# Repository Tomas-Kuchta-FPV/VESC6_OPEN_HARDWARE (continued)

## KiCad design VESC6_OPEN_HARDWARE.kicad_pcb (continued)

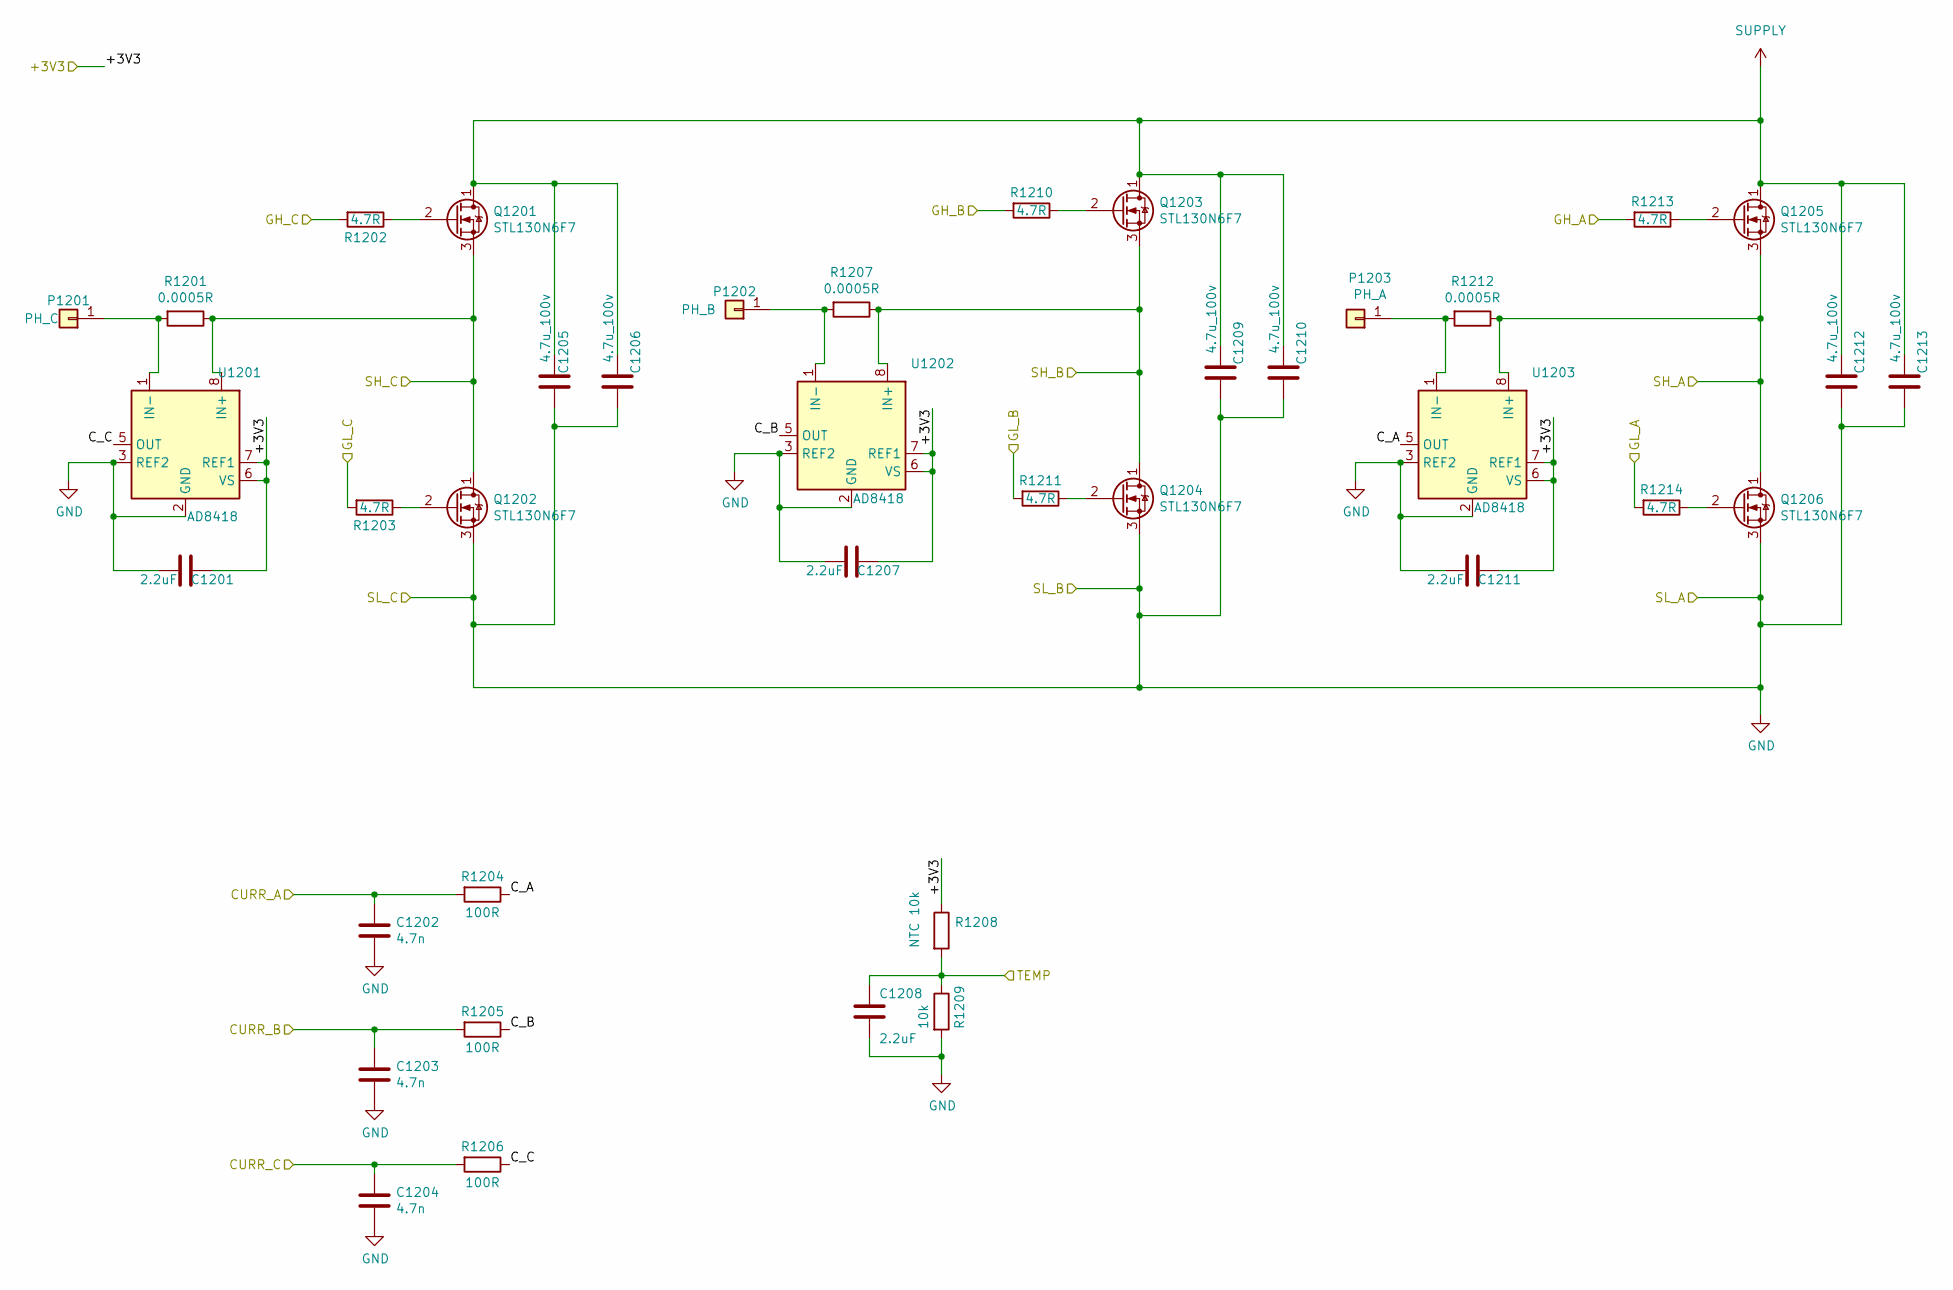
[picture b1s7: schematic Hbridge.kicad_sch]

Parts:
C1201, C1207, C1208, C1211: 2.2uF; C_0603_1608Metric; LCSC C23630
C1202, C1203, C1204: 4.7n; C_0603_1608Metric; LCSC C53987
C1205, C1206, C1209, C1210, C1212, C1213: 4.7u_100v; C_1210_3225Metric; LCSC C385987
P1201: PH_C; Pin_D1.3mm_L11.0mm_LooseFit; LCSC C7200700
P1202: PH_B; Pin_D1.3mm_L11.0mm_LooseFit; LCSC C7200700
P1203: PH_A; Pin_D1.3mm_L11.0mm_LooseFit; LCSC C7200700
Q1201, Q1202, Q1203, Q1204, Q1205, Q1206: STL130N6F7; NVMFS5C612NL; LCSC C501008
R1201, R1207, R1212: 0.0005R; 2512_SHUNT; LCSC C469426
R1202, R1203, R1210, R1211, R1213, R1214: 4.7R; R_0603_1608Metric; LCSC C23164
R1204, R1205, R1206: 100R; R_0603_1608Metric; LCSC C22775
R1208: NTC 10k; R_0603_1608Metric; LCSC C76589
R1209: 10k; R_0603_1608Metric; LCSC C25804
U1201, U1202, U1203: AD8418; SOIC-8_3.9x4.9mm_P1.27mm; LCSC C495342

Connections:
+3V3a: C1201.1, C1207.1, C1211.1, R1208.1, U1201.6 (VS), U1201.7 (REF1), U1202.6 (VS), U1202.7 (REF1), U1203.6 (VS), U1203.7 (REF1); also elsewhere on the board
/CHa/DRV8301/GH_A: R1213.2; also elsewhere on the board
/CHa/DRV8301/GH_B: R1210.2; also elsewhere on the board
/CHa/DRV8301/GH_C: R1202.2; also elsewhere on the board
/CHa/DRV8301/GL_A: R1214.2; also elsewhere on the board
/CHa/DRV8301/GL_B: R1211.2; also elsewhere on the board
/CHa/DRV8301/GL_C: R1203.2; also elsewhere on the board
/CHa/DRV8301/SH_A: Q1205.3 (S), Q1206.1 (D), R1212.1, U1203.8 (IN+); also elsewhere on the board
/CHa/DRV8301/SH_B: Q1203.3 (S), Q1204.1 (D), R1207.1, U1202.8 (IN+); also elsewhere on the board
/CHa/DRV8301/SH_C: Q1201.3 (S), Q1202.1 (D), R1201.1, U1201.8 (IN+); also elsewhere on the board
/CHa/Hbridge/CURR_A: C1202.1, R1204.2; also elsewhere on the board
/CHa/Hbridge/CURR_B: C1203.1, R1205.2; also elsewhere on the board
/CHa/Hbridge/CURR_C: C1204.1, R1206.2; also elsewhere on the board
/CHa/Hbridge/C_A: R1204.1, U1203.5 (OUT)
/CHa/Hbridge/C_B: R1205.1, U1202.5 (OUT)
/CHa/Hbridge/C_C: R1206.1, U1201.5 (OUT)
/CHa/Hbridge/TEMP: C1208.1, R1208.2, R1209.1; also elsewhere on the board
GND: C1201.2, C1202.2, C1203.2, C1204.2, C1205.2, C1206.2, C1207.2, C1208.2, C1209.2, C1210.2, C1211.2, C1212.2, C1213.2, Q1202.3 (S), Q1204.3 (S), Q1206.3 (S), R1209.2, U1201.2 (GND), U1201.3 (REF2), U1202.2 (GND), U1202.3 (REF2), U1203.2 (GND), U1203.3 (REF2); also elsewhere on the board
unnamed: P1201.1 (Pin_1_1), R1201.2, U1201.1 (IN-)
unnamed: P1202.1 (Pin_1_1), R1207.2, U1202.1 (IN-)
unnamed: P1203.1 (Pin_1_1), R1212.2, U1203.1 (IN-)
unnamed: Q1201.2 (G), R1202.1
unnamed: Q1202.2 (G), R1203.1
unnamed: Q1203.2 (G), R1210.1
unnamed: Q1204.2 (G), R1211.1
unnamed: Q1205.2 (G), R1213.1
unnamed: Q1206.2 (G), R1214.1
SUPPLY: C1205.1, C1206.1, C1209.1, C1210.1, C1212.1, C1213.1, Q1201.1 (D), Q1203.1 (D), Q1205.1 (D); also elsewhere on the board

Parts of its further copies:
C2201, C2207, C2208, C2211: 2.2uF; C_0603_1608Metric; LCSC C23630
C2202, C2203, C2204: 4.7n; C_0603_1608Metric; LCSC C53987
C2205, C2206, C2209, C2210, C2212, C2213: 4.7u_100v; C_1210_3225Metric; LCSC C385987
P2201: PH_C; Pin_D1.3mm_L11.0mm_LooseFit; LCSC C7200700
P2202: PH_B; Pin_D1.3mm_L11.0mm_LooseFit; LCSC C7200700
P2203: PH_A; Pin_D1.3mm_L11.0mm_LooseFit; LCSC C7200700
Q2201, Q2202, Q2203, Q2204, Q2205, Q2206: STL130N6F7; NVMFS5C612NL; LCSC C501008
R2201, R2207, R2212: 0.0005R; 2512_SHUNT; LCSC C469426
R2202, R2203, R2210, R2211, R2213, R2214: 4.7R; R_0603_1608Metric; LCSC C23164
R2204, R2205, R2206: 100R; R_0603_1608Metric; LCSC C22775
R2208: NTC 10k; R_0603_1608Metric; LCSC C76589
R2209: 10k; R_0603_1608Metric; LCSC C25804
U2201, U2202, U2203: AD8418; SOIC-8_3.9x4.9mm_P1.27mm; LCSC C495342

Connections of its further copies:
+3V3b: C2201.1, C2207.1, C2211.1, R2208.1, U2201.6 (VS), U2201.7 (REF1), U2202.6 (VS), U2202.7 (REF1), U2203.6 (VS), U2203.7 (REF1); also elsewhere on the board
/CHb/DRV8301/GH_A: R2213.2; also elsewhere on the board
/CHb/DRV8301/GH_B: R2210.2; also elsewhere on the board
/CHb/DRV8301/GH_C: R2202.2; also elsewhere on the board
/CHb/DRV8301/GL_A: R2214.2; also elsewhere on the board
/CHb/DRV8301/GL_B: R2211.2; also elsewhere on the board
/CHb/DRV8301/GL_C: R2203.2; also elsewhere on the board
/CHb/DRV8301/SH_A: Q2205.3 (S), Q2206.1 (D), R2212.1, U2203.8 (IN+); also elsewhere on the board
/CHb/DRV8301/SH_B: Q2203.3 (S), Q2204.1 (D), R2207.1, U2202.8 (IN+); also elsewhere on the board
/CHb/DRV8301/SH_C: Q2201.3 (S), Q2202.1 (D), R2201.1, U2201.8 (IN+); also elsewhere on the board
/CHb/Hbridge/CURR_A: C2202.1, R2204.2; also elsewhere on the board
/CHb/Hbridge/CURR_B: C2203.1, R2205.2; also elsewhere on the board
/CHb/Hbridge/CURR_C: C2204.1, R2206.2; also elsewhere on the board
/CHb/Hbridge/C_A: R2204.1, U2203.5 (OUT)
/CHb/Hbridge/C_B: R2205.1, U2202.5 (OUT)
/CHb/Hbridge/C_C: R2206.1, U2201.5 (OUT)
/CHb/Hbridge/TEMP: C2208.1, R2208.2, R2209.1; also elsewhere on the board
GND: C2201.2, C2202.2, C2203.2, C2204.2, C2205.2, C2206.2, C2207.2, C2208.2, C2209.2, C2210.2, C2211.2, C2212.2, C2213.2, Q2202.3 (S), Q2204.3 (S), Q2206.3 (S), R2209.2, U2201.2 (GND), U2201.3 (REF2), U2202.2 (GND), U2202.3 (REF2), U2203.2 (GND), U2203.3 (REF2); also elsewhere on the board
unnamed: P2201.1 (Pin_1_1), R2201.2, U2201.1 (IN-)
unnamed: P2202.1 (Pin_1_1), R2207.2, U2202.1 (IN-)
unnamed: P2203.1 (Pin_1_1), R2212.2, U2203.1 (IN-)
unnamed: Q2201.2 (G), R2202.1
unnamed: Q2202.2 (G), R2203.1
unnamed: Q2203.2 (G), R2210.1
unnamed: Q2204.2 (G), R2211.1
unnamed: Q2205.2 (G), R2213.1
unnamed: Q2206.2 (G), R2214.1
SUPPLY: C2205.1, C2206.1, C2209.1, C2210.1, C2212.1, C2213.1, Q2201.1 (D), Q2203.1 (D), Q2205.1 (D); also elsewhere on the board

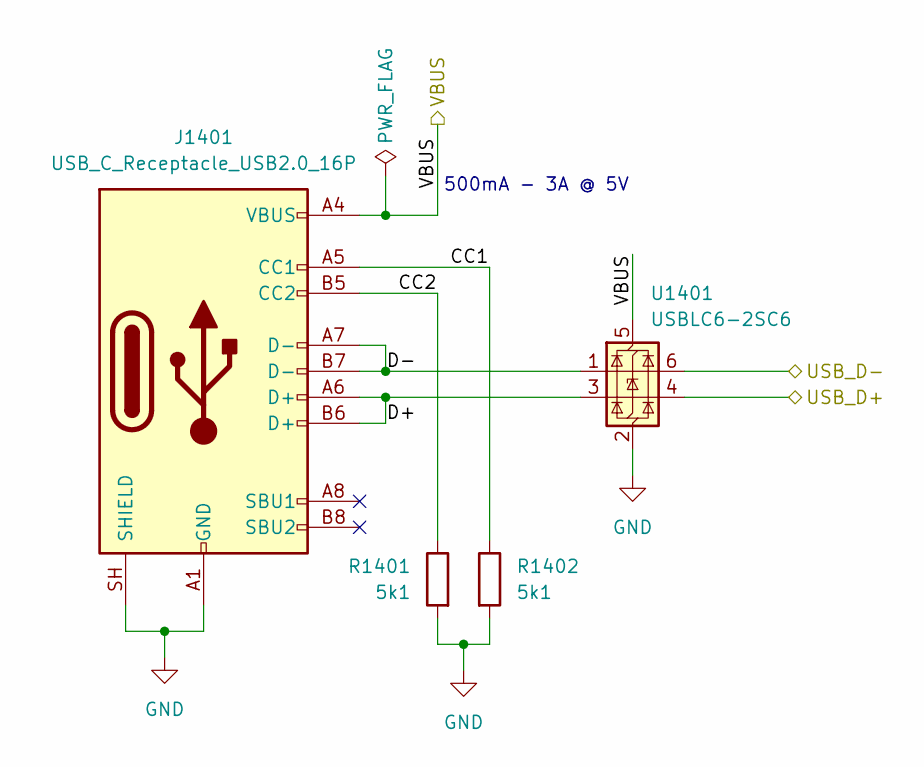
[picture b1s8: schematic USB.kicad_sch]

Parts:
J1401: USB_C_Receptacle_USB2.0_16P; USB_C_Receptacle_HRO_TYPE-C-31-M-12; LCSC part no. C165948
R1401, R1402: 5k1; R_0805_2012Metric_Pad1.20x1.40mm_HandSolder; LCSC part no. C84375
U1401: USBLC6-2SC6; SOT-23-6; LCSC part no. C2827654

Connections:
/CHa/USB/CC1: J1401.A5 (CC1), R1402.1
/CHa/USB/CC2: J1401.B5 (CC2), R1401.1
/CHa/USB/D+: J1401.A6 (D+), J1401.B6 (D+), U1401.3 (I/O2)
/CHa/USB/D-: J1401.A7 (D-), J1401.B7 (D-), U1401.1 (I/O1)
/CHa/USB/USB_D+: U1401.4 (I/O2); also elsewhere on the board
/CHa/USB/USB_D-: U1401.6 (I/O1); also elsewhere on the board
/CHa/USB/VBUS: J1401.A4 (VBUS), J1401.A9 (VBUS), J1401.B4 (VBUS), J1401.B9 (VBUS), U1401.5 (VBUS); also elsewhere on the board
GND: J1401.A1 (GND), J1401.A12 (GND), J1401.B1 (GND), J1401.B12 (GND), J1401.SH (SHIELD), R1401.2, R1402.2, U1401.2 (GND); also elsewhere on the board

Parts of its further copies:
J2401: USB_C_Receptacle_USB2.0_16P; USB_C_Receptacle_HRO_TYPE-C-31-M-12; LCSC part no. C165948
R2401, R2402: 5k1; R_0805_2012Metric_Pad1.20x1.40mm_HandSolder; LCSC part no. C84375
U2401: USBLC6-2SC6; SOT-23-6; LCSC part no. C2827654

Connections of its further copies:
/CHb/USB/CC1: J2401.A5 (CC1), R2402.1
/CHb/USB/CC2: J2401.B5 (CC2), R2401.1
/CHb/USB/D+: J2401.A6 (D+), J2401.B6 (D+), U2401.3 (I/O2)
/CHb/USB/D-: J2401.A7 (D-), J2401.B7 (D-), U2401.1 (I/O1)
/CHb/USB/USB_D+: U2401.4 (I/O2); also elsewhere on the board
/CHb/USB/USB_D-: U2401.6 (I/O1); also elsewhere on the board
/CHb/USB/VBUS: J2401.A4 (VBUS), J2401.A9 (VBUS), J2401.B4 (VBUS), J2401.B9 (VBUS), U2401.5 (VBUS); also elsewhere on the board
GND: J2401.A1 (GND), J2401.A12 (GND), J2401.B1 (GND), J2401.B12 (GND), J2401.SH (SHIELD), R2401.2, R2402.2, U2401.2 (GND); also elsewhere on the board

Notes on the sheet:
500mA - 3A @ 5V

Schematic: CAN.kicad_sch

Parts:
C1001, C1002: 2.2uF; C_0603_1608Metric; LCSC C23630
R1001: 120R; R_0603_1608Metric; LCSC C22787
U1001: TJA1051TK-3; DFN-8-1EP_3x3mm_P0.65mm_EP1.55x2.4mm; LCSC C124020

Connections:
+3V3a: C1002.1, U1001.5 (VIO); also elsewhere on the board
+5Va: C1001.1, U1001.3 (VCC); also elsewhere on the board
/CHa/CAN/RX: U1001.4 (RXD); also elsewhere on the board
/CHa/CAN/TX: U1001.1 (TXD); also elsewhere on the board
/CHa/CANH: R1001.1, U1001.7 (CANH); also elsewhere on the board
/CHa/CANL: R1001.2, U1001.6 (CANL); also elsewhere on the board
GND: C1001.2, C1002.2, U1001.2 (GND), U1001.8 (S), U1001.9 (GND); also elsewhere on the board

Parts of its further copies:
C2001, C2002: 2.2uF; C_0603_1608Metric; LCSC C23630
R2001: 120R; R_0603_1608Metric; LCSC C22787
U2001: TJA1051TK-3; DFN-8-1EP_3x3mm_P0.65mm_EP1.55x2.4mm; LCSC C124020

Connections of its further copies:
+3V3b: C2002.1, U2001.5 (VIO); also elsewhere on the board
+5Vb: C2001.1, U2001.3 (VCC); also elsewhere on the board
/CHa/CANH: R2001.1, U2001.7 (CANH); also elsewhere on the board
/CHa/CANL: R2001.2, U2001.6 (CANL); also elsewhere on the board
/CHb/CAN/RX: U2001.4 (RXD); also elsewhere on the board
/CHb/CAN/TX: U2001.1 (TXD); also elsewhere on the board
GND: C2001.2, C2002.2, U2001.2 (GND), U2001.8 (S), U2001.9 (GND); also elsewhere on the board

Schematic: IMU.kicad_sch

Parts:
C1301, C1302: 100n; C_0603_1608Metric; LCSC C14663; not fitted
R1301, R1302: 1k; R_0603_1608Metric; LCSC C21190; not fitted
U1301: LSM6DS3TR-C; Bosch_LGA-14_3x2.5mm_P0.5mm; LCSC C967633; not fitted

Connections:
+3V3a: C1301.2, C1302.2, R1301.1, R1302.2, U1301.5 (VDDIO), U1301.8 (VDD), U1301.12 (CSB); also elsewhere on the board
/CHa/IMU/SCL: R1301.2, U1301.13 (SCX); also elsewhere on the board
/CHa/IMU/SDA: R1302.1, U1301.14 (SDX); also elsewhere on the board
GND: C1301.1, C1302.1, U1301.1 (SDO), U1301.6 (GNDIO), U1301.7 (GND); also elsewhere on the board

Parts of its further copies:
C2301, C2302: 100n; C_0603_1608Metric; LCSC C14663; not fitted
R2301, R2302: 1k; R_0603_1608Metric; LCSC C21190; not fitted
U2301: LSM6DS3TR-C; Bosch_LGA-14_3x2.5mm_P0.5mm; LCSC C967633; not fitted

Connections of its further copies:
+3V3b: C2301.2, C2302.2, R2301.1, R2302.2, U2301.5 (VDDIO), U2301.8 (VDD), U2301.12 (CSB); also elsewhere on the board
/CHb/IMU/SCL: R2301.2, U2301.13 (SCX); also elsewhere on the board
/CHb/IMU/SDA: R2302.1, U2301.14 (SDX); also elsewhere on the board
GND: C2301.1, C2302.1, U2301.1 (SDO), U2301.6 (GNDIO), U2301.7 (GND); also elsewhere on the board

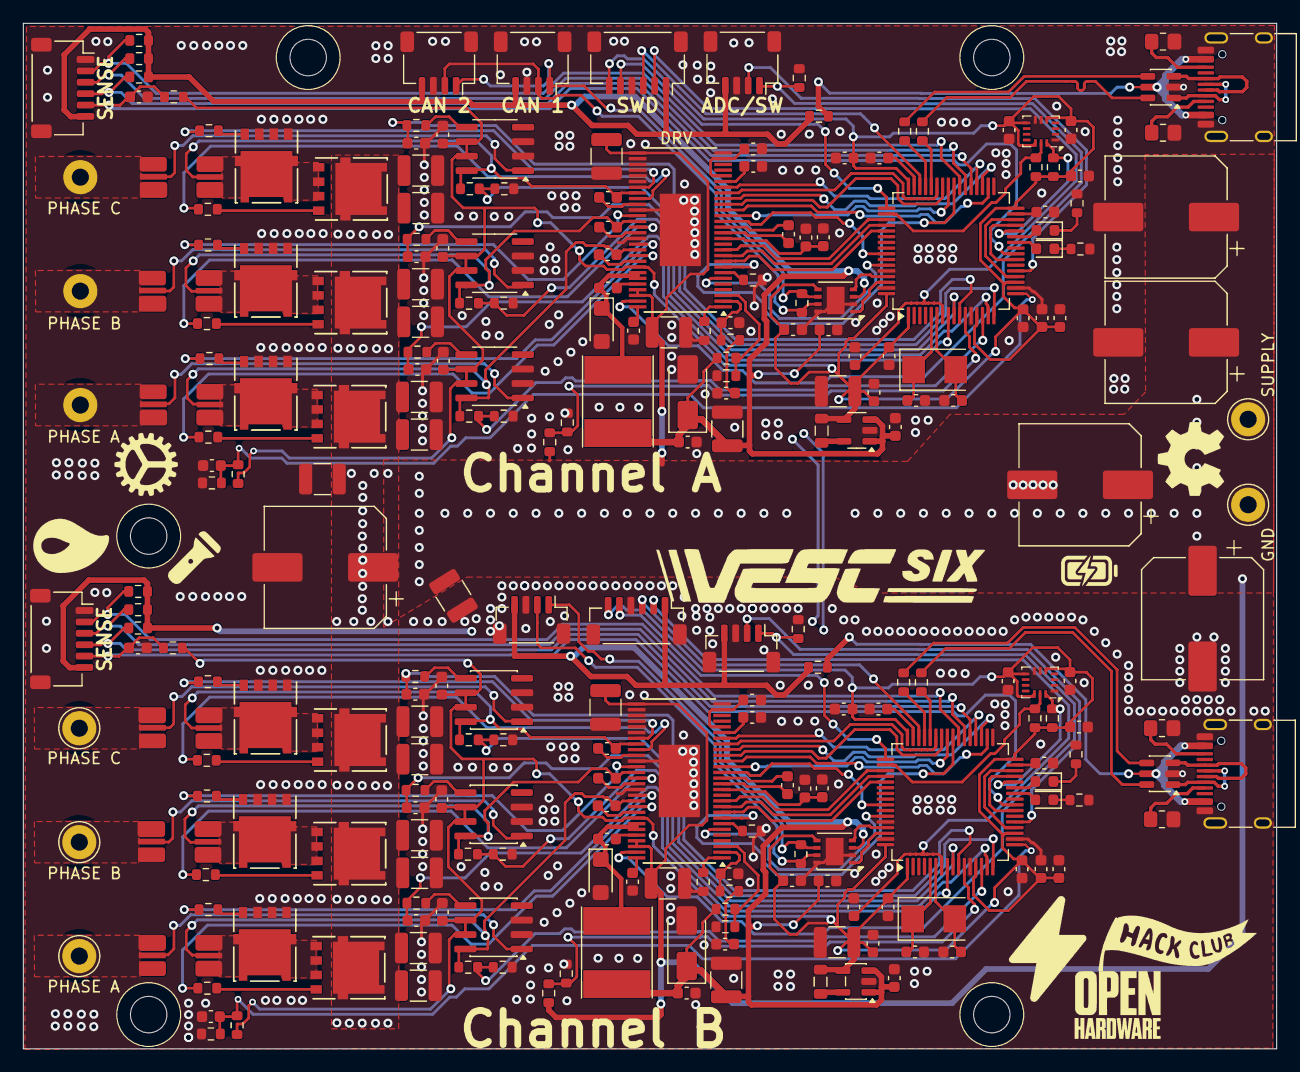
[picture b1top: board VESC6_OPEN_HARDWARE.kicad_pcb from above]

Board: 4 copper layers, 110.0 x 90.0 mm, 255 parts (0 on the bottom side), 188 nets.

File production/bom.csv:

Designator,Footprint,Quantity,Value,LCSC Part #
"C1001, C1002, C1101, C1102, C1103, C1104, C1106, C1109, C1118, C1201, C1207, C1208, C1211, C1502, C1503, C1505, C1506, C1508, C1509, C1510, C1511, C2001, C2002, C2101, C2102, C2103, C2104, C2106, C2109, C2118, C2201, C2207, C2208, C2211, C2502, C2503, C2505, C2506, C2508, C2509, C2510, C2511",0603,42,2.2uF,C23630
"C1105, C2105",0603,2,6.8n,C1631
"C1107, C2107",0603,2,120p,C107035
"C1108, C2108",0603,2,22n,C21122
"C1110, C1119, C2110, C2119",1210,4,100u,C16133
"C1111, C2111",0603,2,15n,C1596
"C1112, C1117, C1205, C1206, C1209, C1210, C1212, C1213, C206, C207, C2112, C2117, C2205, C2206, C2209, C2210, C2212, C2213",1210,18,4.7u_100v,C385987
"C1113, C1114, C1115, C2113, C2114, C2115",0603,6,220n,C21120
"C1116, C1504, C2116, C2504, C301, C401",0603,6,100n,C14663
"C1202, C1203, C1204, C2202, C2203, C2204",0603,6,4.7n,C53987
"C1501, C1507, C2501, C2507",0603,4,15p,C1644
"C201, C202, C203, C204, C205",CP_Elec_10x10.5,5,220u_63v,C7471900
"D1101, D2101",D_SMF,2,DIODE,C2923951
"D1102, D2102",D_SMA,2,TVS 5V,C129544
"D301, D401",0603,2,RED,C2286
"D302, D402",0603,2,WHITE,C2290
"J1401, J2401",USB_C_Receptacle_HRO_TYPE-C-31-M-12,2,USB_C_Receptacle_USB2.0_16P,C165948
"L1101, L2101",0805,2,2.2u,C383398
"L1102, L2102",L_Taiyo-Yuden_NR-60xx_HandSoldering,2,22u,C266430
"P1201, P2201",Pin_D1.3mm_L11.0mm_LooseFit,2,PH_C,C7200700
"P1202, P2202",Pin_D1.3mm_L11.0mm_LooseFit,2,PH_B,C7200700 
"P1203, P2203",Pin_D1.3mm_L11.0mm_LooseFit,2,PH_A,C7200700 
P201,Pin_D1.3mm_L11.0mm_LooseFit,1,SUPPLY,C7200700 
P202,Pin_D1.3mm_L11.0mm_LooseFit,1,GND,C7200700 
P301,JST_SH_SM04B-SRSS-TB_1x04-1MP_P1.00mm_Horizontal,1,CAN 2,C160404
P302,JST_SH_SM04B-SRSS-TB_1x04-1MP_P1.00mm_Horizontal,1,CAN 1,C160404
P303,JST_SH_SM06B-SRSS-TB_1x06-1MP_P1.00mm_Horizontal,1,SWD,C160405
"P304, P404",JST_SH_SM06B-SRSS-TB_1x06-1MP_P1.00mm_Horizontal,2,HALL/Encoder,C160405
P305,JST_SH_SM04B-SRSS-TB_1x04-1MP_P1.00mm_Horizontal,1,ADC_SWITCH,C160404
P401,JST_SH_BM04B-SRSS-TB_1x04-1MP_P1.00mm_Vertical,1,CAN 1,C160390
P403,JST_SH_BM06B-SRSS-TB_1x06-1MP_P1.00mm_Vertical,1,SWD,C160392
P405,JST_SH_BM04B-SRSS-TB_1x04-1MP_P1.00mm_Vertical,1,ADC_SWITCH,C160390
"Q1201, Q1202, Q1203, Q1204, Q1205, Q1206, Q2201, Q2202, Q2203, Q2204, Q2205, Q2206",NVMFS5C612NL,12,STL130N6F7,C501008
"R1001, R2001, R308, R309, R408, R409",0603,6,120R,C22787
"R1101, R2101",0603,2,3.3k,C22978
"R1102, R2102",0603,2,18k,C25810
"R1103, R2103",0603,2,15k,C22809
"R1104, R1106, R1209, R2104, R2106, R2209, R307, R407",0603,8,10k,C25804
"R1105, R2105",0603,2,220k,C22961
"R1107, R1109, R1111, R1113, R2107, R2109, R2111, R2113",0603,8,39k,C23153
"R1108, R1110, R1112, R1114, R2108, R2110, R2112, R2114, R301, R302, R303, R401, R402, R403",0603,14,2k2,C4190
"R1201, R1207, R1212, R2201, R2207, R2212",2512_SHUNT,6,0.0005R,C469426
"R1202, R1203, R1210, R1211, R1213, R1214, R2202, R2203, R2210, R2211, R2213, R2214",0603,12,4.7R,C23164
"R1204, R1205, R1206, R2204, R2205, R2206",0603,6,100R,C22775
"R1208, R2208",0603,2,NTC 10k,C76589
"R1401, R1402, R2401, R2402",0805,4,5k1,C84375
"R304, R404",0603,2,DNP,
"R305, R306, R405, R406",0603,4,22R,C23345
"U1001, U2001",DFN-8-1EP_3x3mm_P0.65mm_EP1.55x2.4mm,2,TJA1051TK-3,C124020
"U1101, U2101",SOT-23-5,2,LM3671,C477918
"U1102, U2102",HTSSOP-56-1EP_6.1x14mm_P0.5mm_EP3.61x6.35mm,2,DRV8301,C98969
"U1201, U1202, U1203, U2201, U2202, U2203",SOIC-8_3.9x4.9mm_P1.27mm,6,AD8418,C495342
"U1401, U2401",SOT-23-6,2,USBLC6-2SC6,C2827654
"U1501, U2501",LQFP-64_10x10mm_P0.5mm,2,STM32F40X_LQFP64,C15742
"X1501, X2501",Crystal_SMD_5032-2Pin_5.0x3.2mm,2,8m,C115962
